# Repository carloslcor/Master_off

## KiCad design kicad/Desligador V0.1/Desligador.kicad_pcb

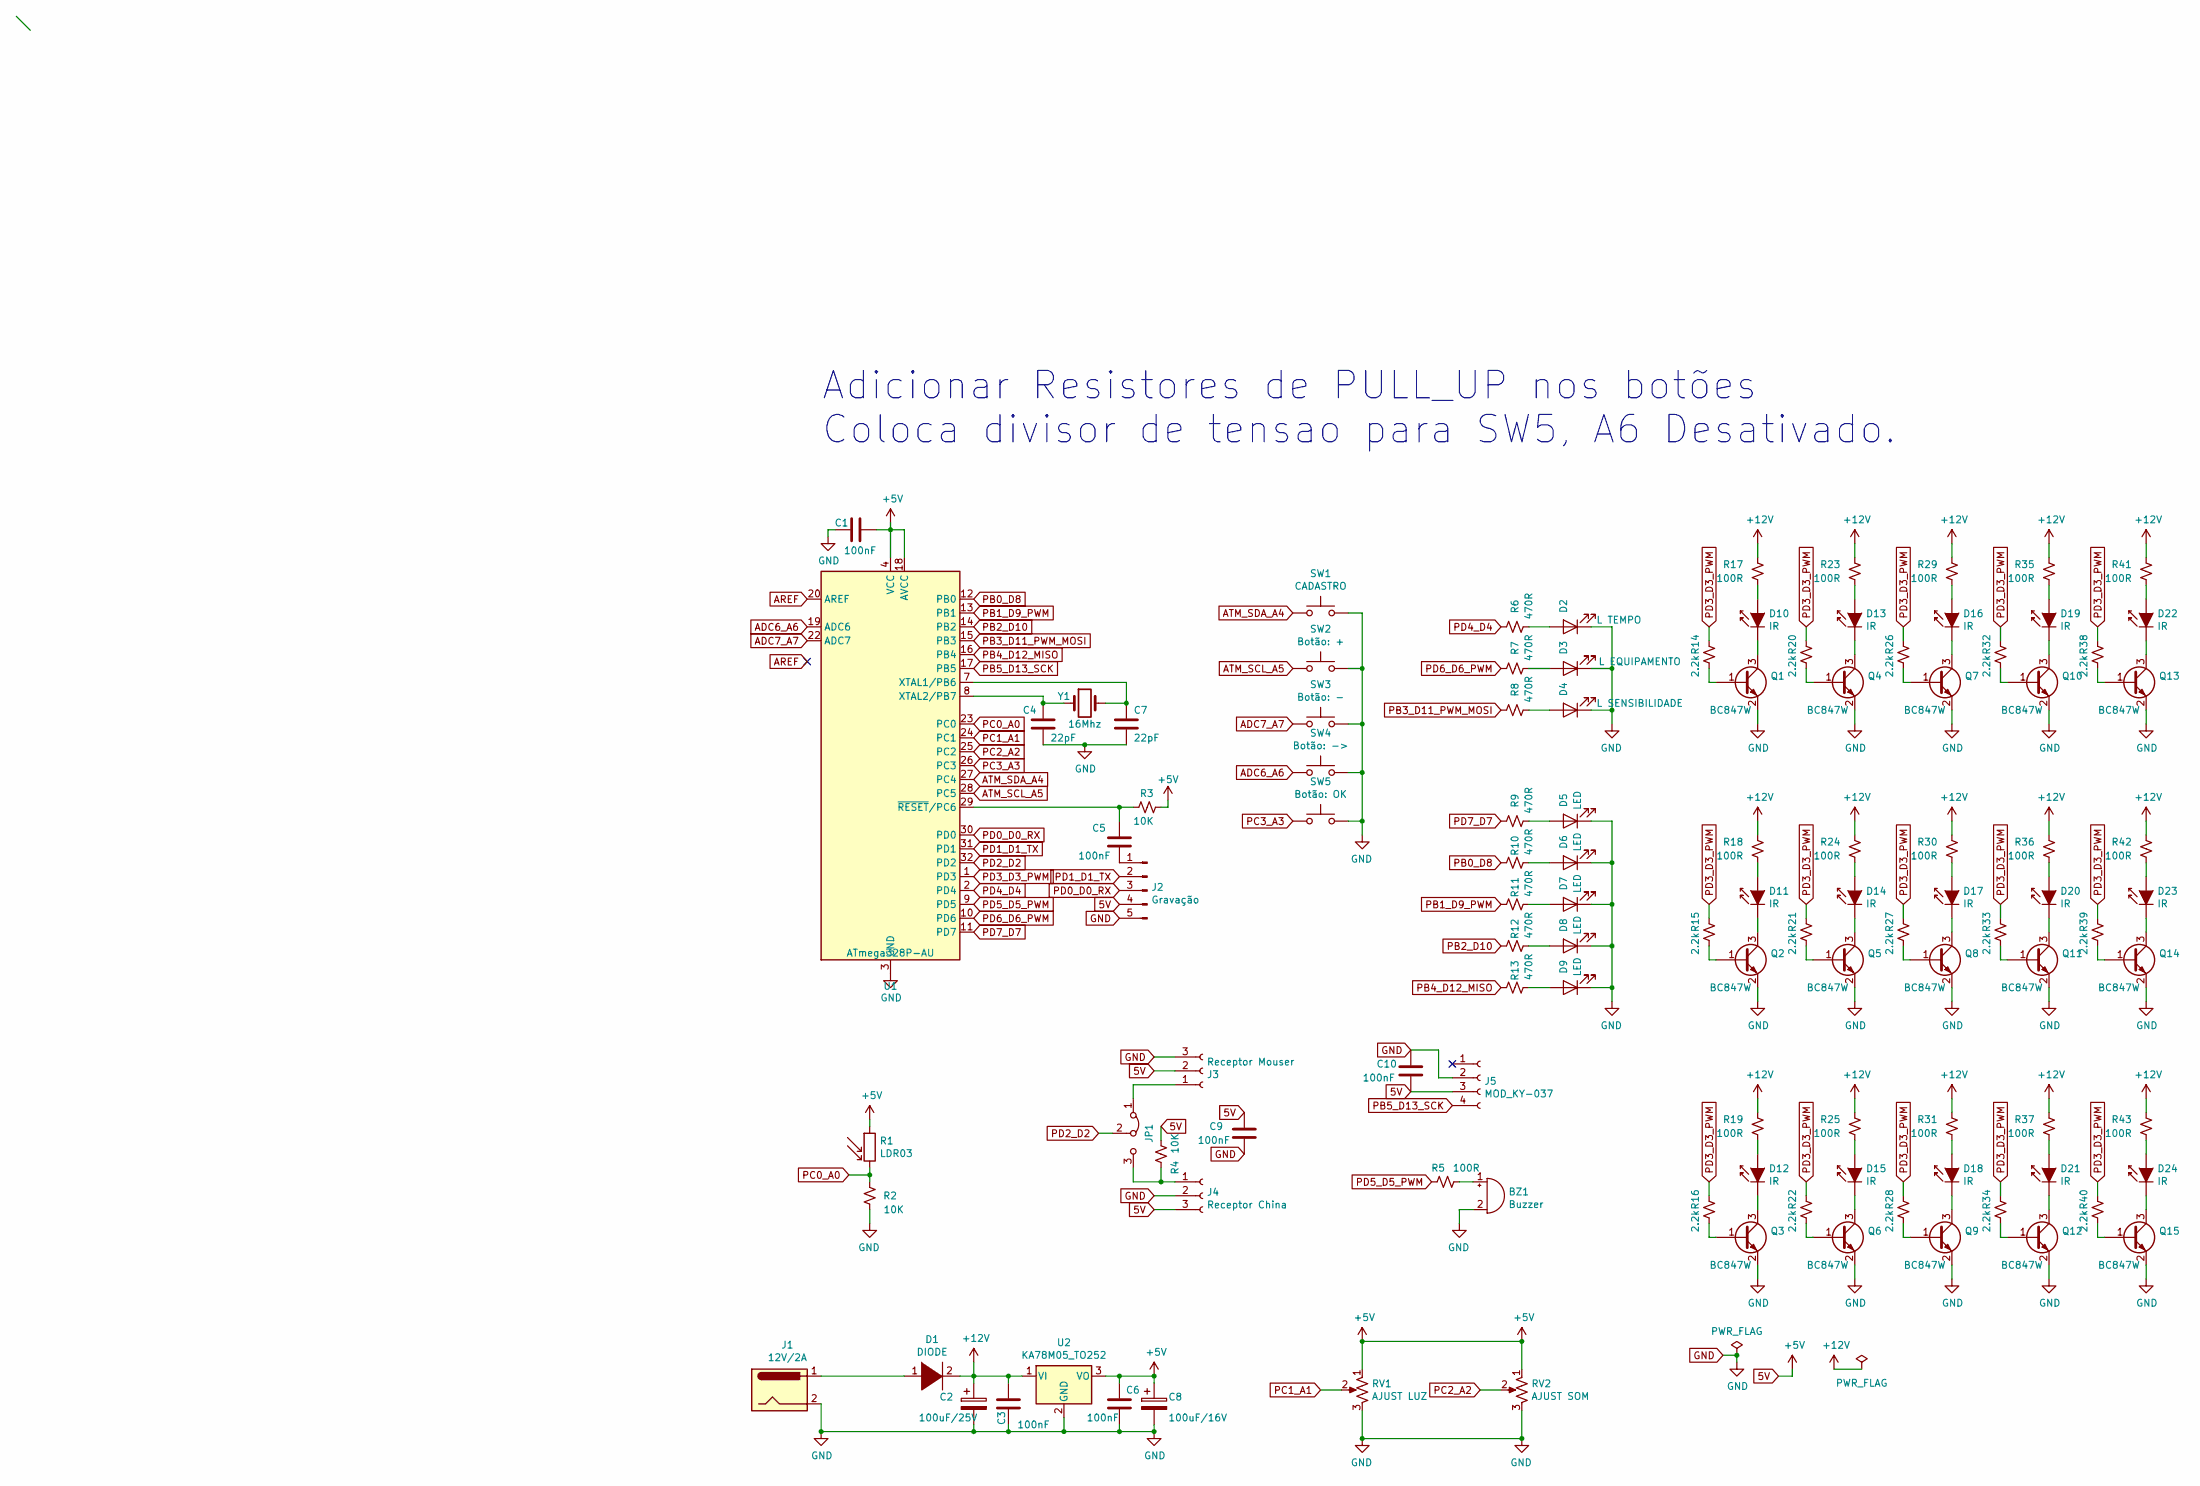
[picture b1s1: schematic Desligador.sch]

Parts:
BZ1: Buzzer; Buzzer_12x9.5RM7.6
C1, C3, C5, C6, C9, C10: 100nF; C_0805_2012Metric_Pad1.15x1.40mm_HandSolder
C2: 100uF/25V; CP_Radial_D6.3mm_P2.50mm
C4, C7: 22pF; C_0805_2012Metric_Pad1.15x1.40mm_HandSolder
C8: 100uF/16V; CP_Radial_D6.3mm_P2.50mm; Part_Num UKL1E101KPD1TA
D1: DIODE; D_DO-41_SOD81_P2.54mm_Vertical_KathodeUp; Part_Num 1N4007E-E3/54
D2: L TEMPO; LED_D3.0mm
D3: L EQUIPAMENTO; LED_D3.0mm
D4: L SENSIBILIDADE; LED_D3.0mm
D5, D6, D7, D8, D9: LED; LED_D3.0mm
D10, D11, D12, D13, D14, D15, D16, D17, D18, D19, D20, D21: IR; LED_D5.0mm_Horizontal_O6.35mm_Z9.0mm
D22, D23, D24: IR; LED_D5.0mm_Clear
J1: 12V/2A; Molex_KK-254_AE-6410-02A_1x02_P2.54mm_Vertical
J2: Gravação; PinHeader_1x05_P2.54mm_Vertical
J3: Receptor Mouser; PinHeader_1x03_P2.54mm_Vertical; Part_Num TSOP32138
J4: Receptor China; PinHeader_1x03_P2.54mm_Vertical; Part_Num HX1838
J5: MOD_KY-037; PinHeader_1x04_P2.54mm_Vertical
JP1: Jumper_3_Bridged12; PinHeader_1x03_P2.54mm_Vertical
Q1, Q2, Q3, Q4, Q5, Q6, Q7, Q8, Q9, Q10, Q11, Q12, Q13, Q14, Q15: BC847W; SOT-23
R1: LDR03; R_LDR_5.1x4.3mm_P3.4mm_Vertical
R2, R3, R4: 10K; R_0805_2012Metric_Pad1.15x1.40mm_HandSolder
R5, R17, R18, R19, R23, R24, R25, R29, R30, R31, R35, R36, R37, R41, R42, R43: 100R; R_0805_2012Metric_Pad1.15x1.40mm_HandSolder
R6, R7, R8, R9, R10, R11, R12, R13: 470R; R_0805_2012Metric_Pad1.15x1.40mm_HandSolder
R14, R15, R16, R20, R21, R22, R26, R27, R28, R32, R33, R34, R38, R39, R40: 2.2k; R_0805_2012Metric_Pad1.15x1.40mm_HandSolder
RV1: AJUST LUZ; PinHeader_1x03_P2.54mm_Vertical
RV2: AJUST SOM; PinHeader_1x03_P2.54mm_Vertical
SW1: CADASTRO; SW_PUSH_6mm_H5mm
SW2: Botão: +; SW_PUSH_6mm_H5mm
SW3: Botão: -; SW_PUSH_6mm_H5mm
SW4: Botão: ->; SW_PUSH_6mm_H5mm
SW5: Botão: OK; SW_PUSH_6mm_H5mm
U1: ATmega328P-AU; TQFP-32_7x7mm_P0.8mm
U2: KA78M05_TO252; TO-252-2; Part_Num MC78M05CDTRKG
Y1: 16Mhz; Crystal_HC49-4H_Vertical

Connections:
5V: C1.2, C6.2, C8.1, C9.2, C10.2, J2.4, J3.2, J4.3, J5.3, R1.1, R3.2, R4.1, RV1.1, RV2.1, U1.4 (VCC), U1.6 (VCC), U1.18 (AVCC), U2.3 (VO)
+12V: C2.1, C3.2, D1.2 (A), R17.2, R18.2, R19.2, R23.2, R24.2, R25.2, R29.2, R30.2, R31.2, R35.2, R36.2, R37.2, R41.2, R42.2, R43.2, U2.1 (VI)
ADC6_A6: SW4.1, U1.19 (ADC6)
ADC7_A7: SW3.1, U1.22 (ADC7)
AREF: U1.20 (AREF)
ATM_SCL_A5: SW2.1, U1.28 (PC5)
ATM_SDA_A4: SW1.1, U1.27 (PC4)
GND: BZ1.2 (+), C1.1, C2.2, C3.1, C4.2, C6.1, C7.2, C8.2, C9.1, C10.1, D2.1 (K), D3.1 (K), D4.1 (K), D5.1 (K), D6.1 (K), D7.1 (K), D8.1 (K), D9.1 (K), J1.2, J2.5, J3.3, J4.2, J5.2, Q1.2 (E), Q2.2 (E), Q3.2 (E), Q4.2 (E), Q5.2 (E), Q6.2 (E), Q7.2 (E), Q8.2 (E), Q9.2 (E), Q10.2 (E), Q11.2 (E), Q12.2 (E), Q13.2 (E), Q14.2 (E), Q15.2 (E), R2.1, RV1.3, RV2.3, SW1.2, SW2.2, SW3.2, SW4.2, SW5.2, U1.3 (GND), U1.5 (GND), U1.21 (GND), U2.2 (GND)
unnamed: BZ1.1 (-), R5.2
unnamed: C4.1, U1.8 (XTAL2/PB7), Y1.1
unnamed: C5.1, R3.1, U1.29 (~RESET~/PC6)
unnamed: C5.2, J2.1
unnamed: C7.1, U1.7 (XTAL1/PB6), Y1.2
unnamed: D1.1 (K), J1.1
unnamed: D2.2 (A), R6.1
unnamed: D3.2 (A), R7.1
unnamed: D4.2 (A), R8.1
unnamed: D5.2 (A), R9.1
unnamed: D6.2 (A), R10.1
unnamed: D7.2 (A), R11.1
unnamed: D8.2 (A), R12.1
unnamed: D9.2 (A), R13.1
unnamed: D10.1 (K), Q1.3 (C)
unnamed: D10.2 (A), R17.1
unnamed: D11.1 (K), Q2.3 (C)
unnamed: D11.2 (A), R18.1
unnamed: D12.1 (K), Q3.3 (C)
unnamed: D12.2 (A), R19.1
unnamed: D13.1 (K), Q4.3 (C)
unnamed: D13.2 (A), R23.1
unnamed: D14.1 (K), Q5.3 (C)
unnamed: D14.2 (A), R24.1
unnamed: D15.1 (K), Q6.3 (C)
unnamed: D15.2 (A), R25.1
unnamed: D16.1 (K), Q7.3 (C)
unnamed: D16.2 (A), R29.1
unnamed: D17.1 (K), Q8.3 (C)
unnamed: D17.2 (A), R30.1
unnamed: D18.1 (K), Q9.3 (C)
unnamed: D18.2 (A), R31.1
unnamed: D19.1 (K), Q10.3 (C)
unnamed: D19.2 (A), R35.1
unnamed: D20.1 (K), Q11.3 (C)
unnamed: D20.2 (A), R36.1
unnamed: D21.1 (K), Q12.3 (C)
unnamed: D21.2 (A), R37.1
unnamed: D22.1 (K), Q13.3 (C)
unnamed: D22.2 (A), R41.1
unnamed: D23.1 (K), Q14.3 (C)
unnamed: D23.2 (A), R42.1
unnamed: D24.1 (K), Q15.3 (C)
unnamed: D24.2 (A), R43.1
unnamed: J3.1, JP1.1 (A)
unnamed: J4.1, JP1.3 (B), R4.2
unnamed: Q1.1 (B), R14.1
unnamed: Q2.1 (B), R15.1
unnamed: Q3.1 (B), R16.1
unnamed: Q4.1 (B), R20.1
unnamed: Q5.1 (B), R21.1
unnamed: Q6.1 (B), R22.1
unnamed: Q7.1 (B), R26.1
unnamed: Q8.1 (B), R27.1
unnamed: Q9.1 (B), R28.1
unnamed: Q10.1 (B), R32.1
unnamed: Q11.1 (B), R33.1
unnamed: Q12.1 (B), R34.1
unnamed: Q13.1 (B), R38.1
unnamed: Q14.1 (B), R39.1
unnamed: Q15.1 (B), R40.1
PB0_D8: R10.2, U1.12 (PB0)
PB1_D9_PWM: R11.2, U1.13 (PB1)
PB2_D10: R12.2, U1.14 (PB2)
PB3_D11_PWM_MOSI: R8.2, U1.15 (PB3)
PB4_D12_MISO: R13.2, U1.16 (PB4)
PB5_D13_SCK: J5.4, U1.17 (PB5)
PC0_A0: R1.2, R2.2, U1.23 (PC0)
PC1_A1: RV1.2, U1.24 (PC1)
PC2_A2: RV2.2, U1.25 (PC2)
PC3_A3: SW5.1, U1.26 (PC3)
PD0_D0_RX: J2.3, U1.30 (PD0)
PD1_D1_TX: J2.2, U1.31 (PD1)
PD2_D2: JP1.2 (C), U1.32 (PD2)
PD3_D3_PWM: R14.2, R15.2, R16.2, R20.2, R21.2, R22.2, R26.2, R27.2, R28.2, R32.2, R33.2, R34.2, R38.2, R39.2, R40.2, U1.1 (PD3)
PD4_D4: R6.2, U1.2 (PD4)
PD5_D5_PWM: R5.1, U1.9 (PD5)
PD6_D6_PWM: R7.2, U1.10 (PD6)
PD7_D7: R9.2, U1.11 (PD7)

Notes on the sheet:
Adicionar Resistores de PULL_UP nos botões Coloca divisor de tensao para SW5, A6 Desativado.

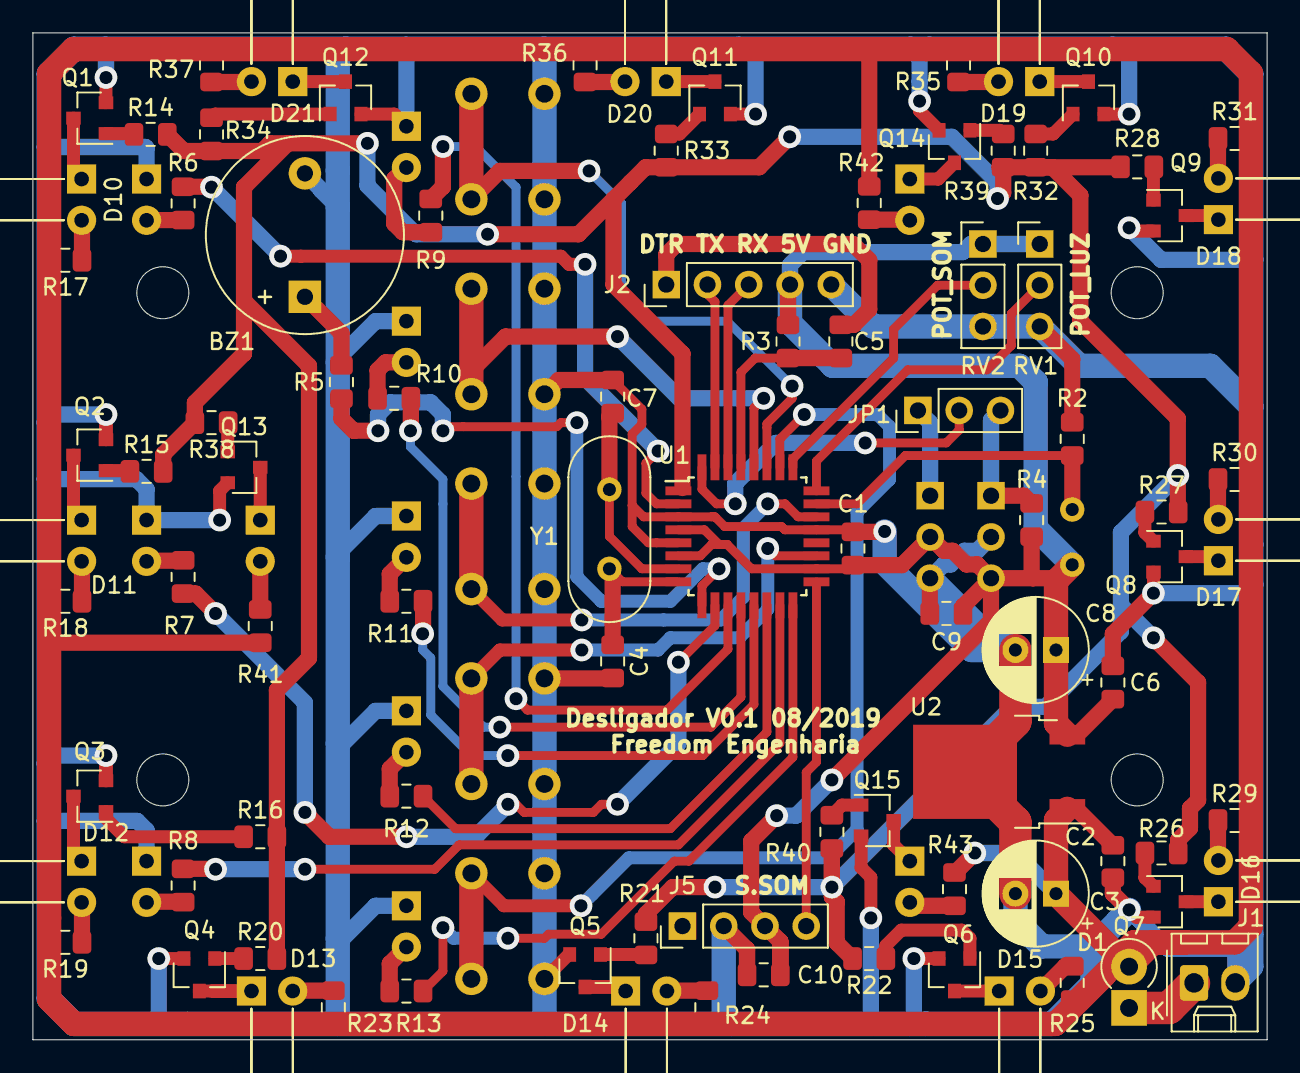
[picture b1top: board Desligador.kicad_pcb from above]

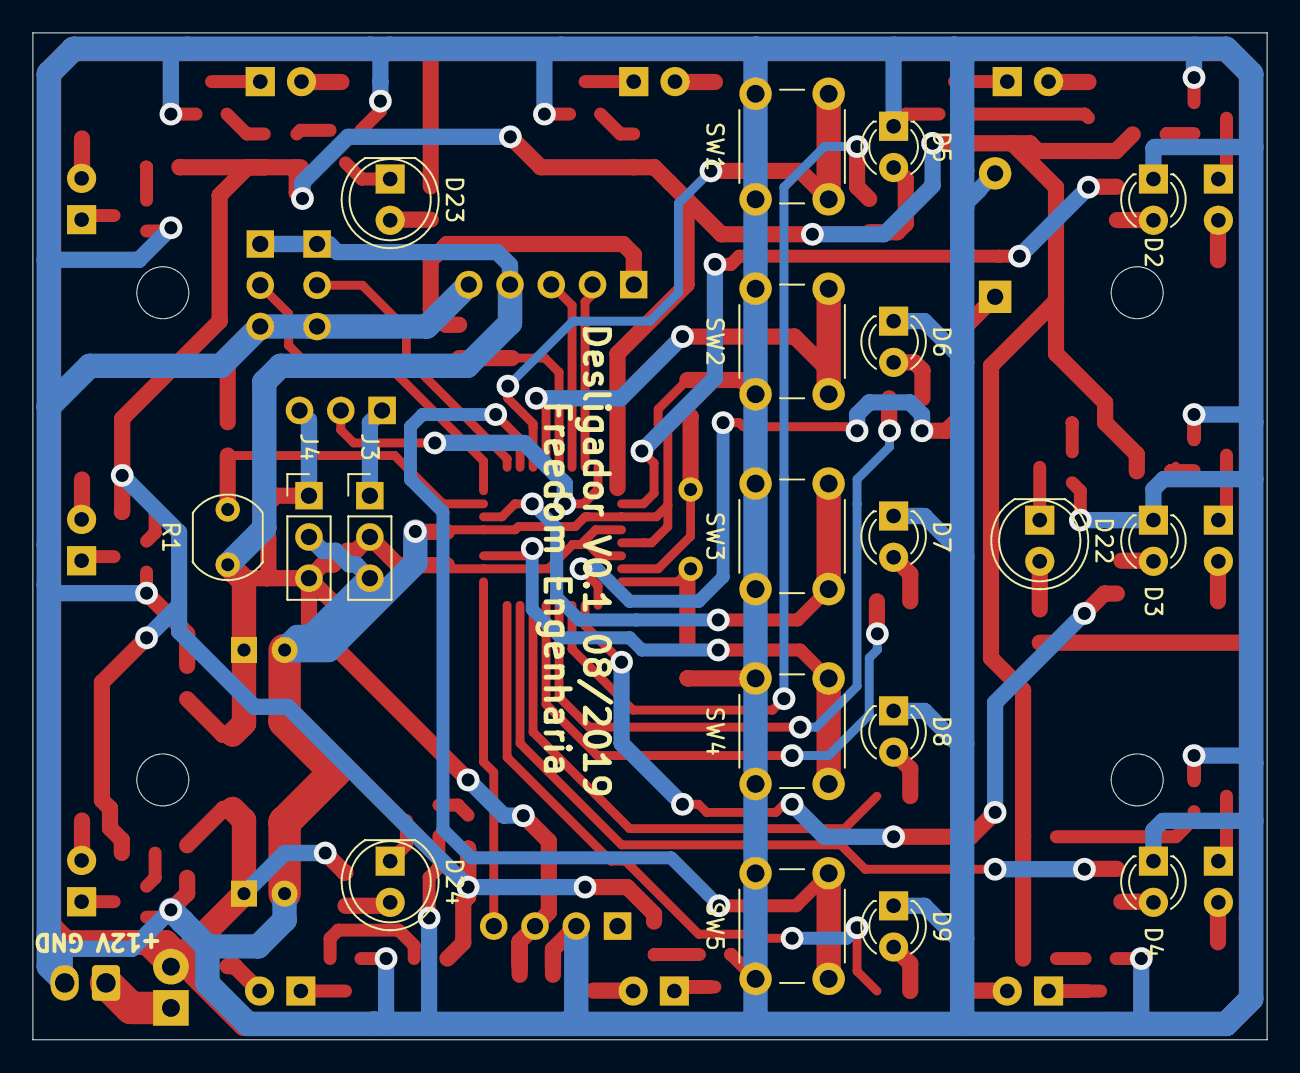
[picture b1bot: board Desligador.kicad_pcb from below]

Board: 2 copper layers, 76.0 x 62.0 mm, 109 parts (19 on the bottom side), 86 nets.

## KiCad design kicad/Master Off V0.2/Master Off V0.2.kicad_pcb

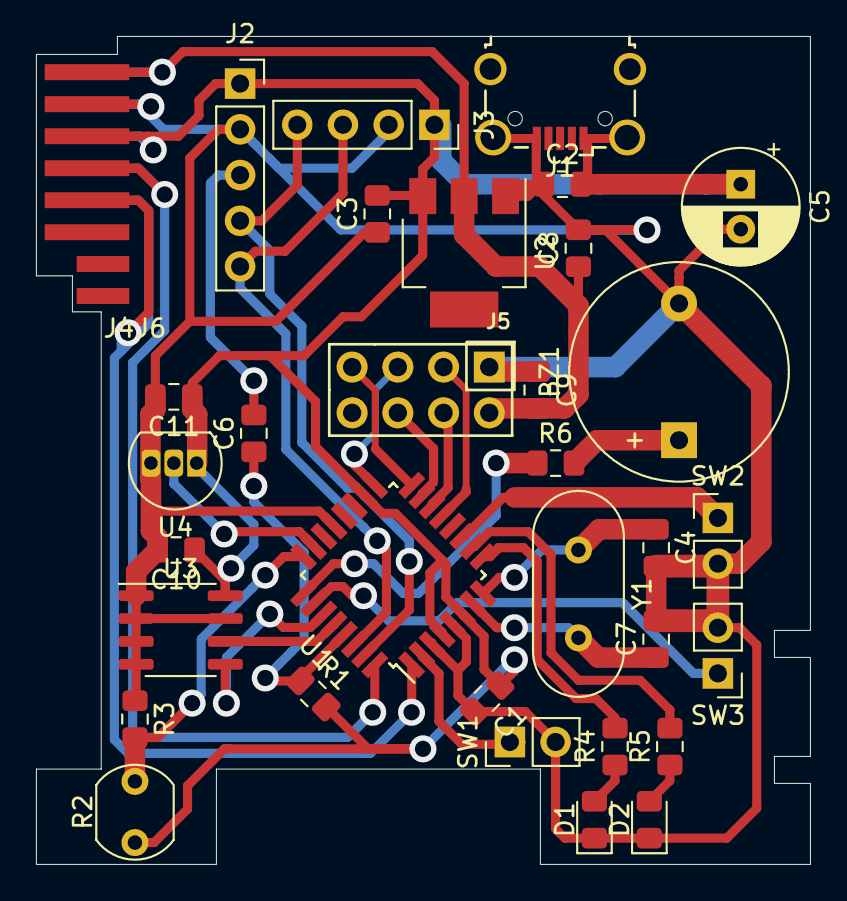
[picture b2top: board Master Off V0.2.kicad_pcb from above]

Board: 2 copper layers, 43.0 x 46.0 mm, 34 parts (0 on the bottom side), 29 nets.

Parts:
BZ1: Buzzer; Buzzer_12x9.5RM7.6
C1, C2, C3, C6, C8, C9, C10, C11: 100nF; C_0805_2012Metric_Pad1.15x1.40mm_HandSolder
C4, C7: 22pF; C_0805_2012Metric_Pad1.15x1.40mm_HandSolder
C5: 100uF/16V; CP_Radial_D6.3mm_P2.50mm
D1: L MENU0; LED_0805_2012Metric_Pad1.15x1.40mm_HandSolder
D2: L MENU1; LED_0805_2012Metric_Pad1.15x1.40mm_HandSolder
J1: USB_B_Micro; USB_Micro-B_Wuerth_629105150521_CircularHoles
J2: Gravação; PinSocket_1x05_P2.54mm_Vertical
J3: Bluetooh; PinSocket_1x04_P2.54mm_Vertical
J4: Conexão PCI TOP; CONEXAO_RMMINI3_TOP
J5: Conn_02x04_Odd_Even; NRF24L01_MOD
J6: Conexão PCI BOT; CONEXAO_RMMINI3_BOT
R1, R3: 10K; R_0805_2012Metric_Pad1.15x1.40mm_HandSolder
R2: LDR03; R_LDR_5.1x4.3mm_P3.4mm_Vertical
R4, R5: 470R; R_0805_2012Metric_Pad1.15x1.40mm_HandSolder
R6: 100R; R_0805_2012Metric_Pad1.15x1.40mm_HandSolder
SW1: MENU1; PinHeader_1x02_P2.54mm_Vertical
SW2: MENU2; PinHeader_1x02_P2.54mm_Vertical
SW3: MENU3; PinHeader_1x02_P2.54mm_Vertical
U1: ATmega328P-AU; TQFP-32_7x7mm_P0.8mm
U2: AZ1117-3.3; SOT-223
U3: AT24CS32-SSHM; SOIC-8_3.9x4.9mm_P1.27mm
U4: LM35-LP; TO-92L_Inline
Y1: 16Mhz; Crystal_HC49-4H_Vertical

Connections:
3v3: C8.1, C9.2, J4.1, J5.2, J6.1, U2.2
5V: C1.2, C2.2, C3.2, C5.1, C10.1, C11.1, J1.1, J2.1, J3.1, J4.3, J6.3, R1.2, R2.1, U1.4, U1.6, U1.18, U2.3, U3.8, U4.1
ATM_SCL_A5: U1.28, U3.6
ATM_SDA_A4: U1.27, U3.5
GND: BZ1.2, C1.1, C2.1, C3.1, C4.2, C5.2, C7.2, C8.2, C9.1, C10.2, C11.2, D1.1, D2.1, J1.5, J2.2, J3.2, J4.2, J5.1, J6.2, R3.1, SW1.2, SW2.2, SW3.2, U1.3, U1.5, U1.21, U2.1, U3.1, U3.2, U3.3, U3.4, U3.7, U4.3
unnamed: BZ1.1, R6.2
unnamed: C4.1, U1.8, Y1.1
unnamed: C6.1, R1.1, U1.29
unnamed: C6.2, J2.3
unnamed: C7.1, U1.7, Y1.2
unnamed: D1.2, R4.1
unnamed: D2.2, R5.1
PB1_D9_PWM: J5.3, U1.13
PB2_D10_PWM: J5.4, U1.14
PB3_D11_PWM_MOSI: J5.6, U1.15
PB4_D12_MISO: J5.7, U1.16
PB5_D13_SCK: J5.5, U1.17
PC0_A0: U1.23, U4.2
PC1_A1: R2.2, R3.2, U1.24
PC2_A2: R6.1, U1.25
PC3_A3: SW3.1, U1.26
PD0_D0_RX: J2.5, J3.3, U1.30
PD1_D1_TX: J2.4, J3.4, U1.31
PD2_D2: J4.4, J6.4, U1.32
PD3_D3_PWM: J4.5, J6.5, U1.1
PD4_D4: SW1.1, U1.2
PD5_D5_PWM: R4.2, U1.9
PD6_D6_PWM: R5.2, U1.10
PD7_D7: SW2.1, U1.11

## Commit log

2020-08-22 Primeiro Commit
